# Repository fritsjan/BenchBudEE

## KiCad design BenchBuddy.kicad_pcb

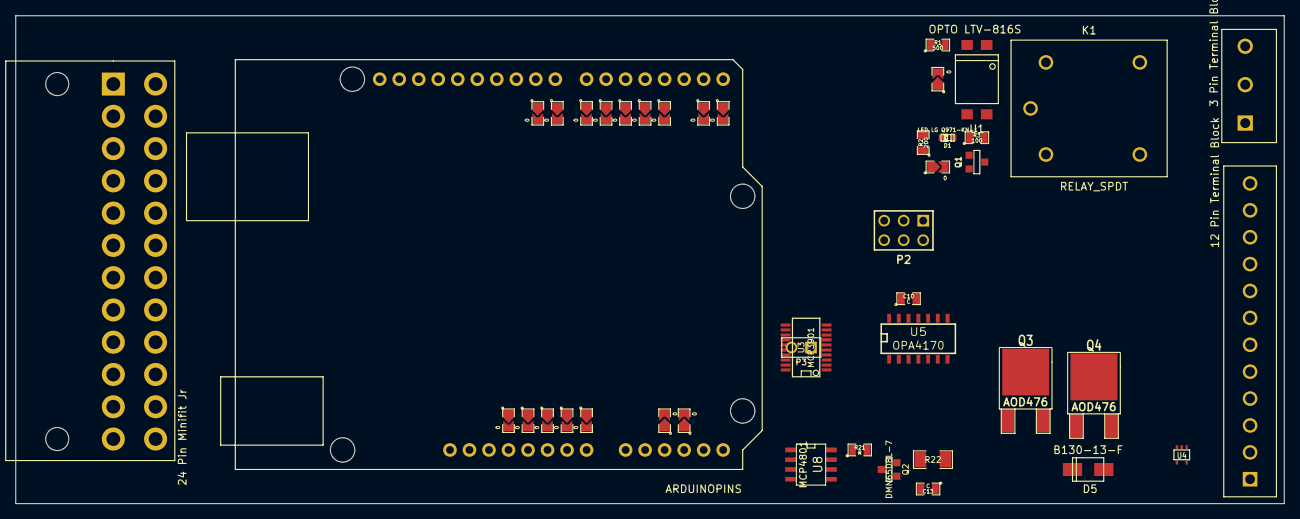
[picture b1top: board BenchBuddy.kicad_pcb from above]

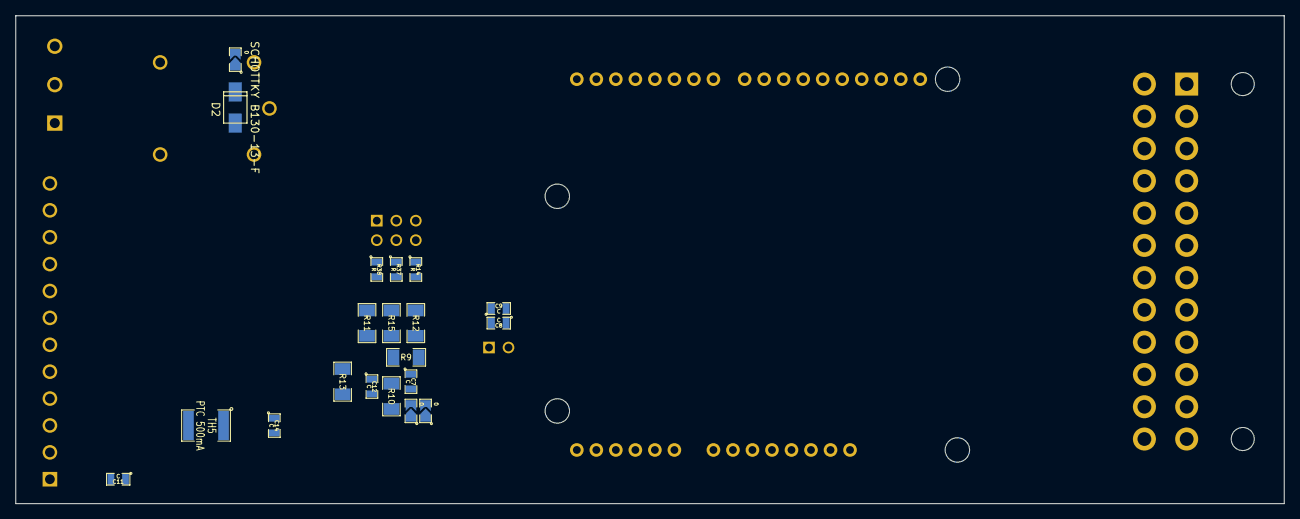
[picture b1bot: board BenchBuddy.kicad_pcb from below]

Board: 4 copper layers, 165.1 x 63.5 mm, 63 parts (20 on the bottom side), 66 nets, no tracks yet.

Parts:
C7, C8, C9, C10, C11, C12, C13, C14: C; SM0805
D1: LED LG Q971-KN-1; LED-0603
D2: SCHOTTKY B130-13-F; SMA
D5: B130-13-F; SMA
K1: RELAY_SPDT; TE-SPDT
K2: 3 Pin Terminal Block; 3pinTB
P1: 24 Pin Minifit Jr; 24pin-ATX
P2: CONN_3X2; pin_array_3x2
P3: CONN_2; PIN_ARRAY_2X1
P4: 12 Pin Terminal Block; 12pinTB
Q1: MMBT3904-7-F; SOT23EBC
Q2: DMN65D8L-7; SOT23GDS
Q3, Q4: AOD476; DPAK2
R1: 500; SM0805
R2: 200; SM0805
R3: 100; SM0805
R4, R5, R6, R23, R24, R25, R26, R27, R28, R29, R30, R31, R32, R33, R34, R35, R36, R39, R40, R41, R42: 0; S_Jumper_SM0805
R9, R10, R11, R12, R13, R15: R; SM1206
R14, R21, R37, R38: R; SM0805
R22: 1; SM1206
TH5: PTC 500mA; SM1812
U1: OPTO LTV-816S; 4-SMD
U3: MCP3901; SSOP20
U4: LMT84; SOT353
U5: OPA4170; SO14E
U8: MCP4801; SO8E
U10: ARDUINOPINS; ArduinoUnoR3

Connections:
+5V: C8.2, C9.1, C11.1, C13.2, P4.1, U3.2, U3.3, U4.4, U8.1
+12C: C14.2, P1.10, TH5.1
+12P: R4.2, R6.2, R23.1
+12V: C12.1, U5.4
-12V: C10.2, U5.11
/Arduino/CURR_MEAS: Q3.2, Q4.3, R22.1, R26.1
/Arduino/FAN_MODE: Q3.1, R36.2
/Arduino/FAN_PWM_N: Q2.G, R31.2
/Arduino/MISO: R30.2, U3.19
/Arduino/MOSI: R29.2, U3.20, U8.4
/Arduino/RELAY+: R35.2, U1.1
/Arduino/SCLK: R28.2, U3.18, U8.3
/Arduino/~ADC_CS: R33.2, U3.17
/Arduino/~DR: R40.2, U3.14
/Fan/CS_N: R34.2, U8.2
/Fan/FAN_OUT+: D5.2, TH5.2
/Fan/FAN_OUT-: D5.1, Q4.2
/Relay/RELAY_COM: K1.1, K2.1
/Relay/RELAY_NC: K1.4, K2.2
/TerminalBlock/RELAY_NC: K1.3, K2.3
/Thermalcouple/CH0+: C7.1, R9.1, U3.4, U5.1
/Thermalcouple/CH0-: C7.2, R42.2, U3.5
/Thermalcouple/CH1+: U3.6, U4.3
/Thermalcouple/CH1-: R41.2, U3.7
/Thermalcouple/TC IN +: P4.11, U5.10
AGND: C8.1, C9.2, C10.1, C11.2, C12.2, C13.1, C14.1, Q2.S, Q3.3, R10.1, R22.2, R41.1, R42.1, U3.8, U3.11, U4.1, U4.2, U4.5, U8.7
GND: P1.3, P1.5, P4.3, R1.1, R2.1, R5.1
unnamed: R35.1, U10.12
unnamed: R36.1, U10.11
unnamed: R31.1, U10.21
unnamed: R33.1, U10.19
unnamed: R27.2, U10.8
unnamed: R26.2, U10.7
unnamed: R39.1, U10.16
unnamed: R23.2, U10.4
unnamed: R40.1, U10.15
unnamed: R28.1, U10.24
unnamed: R25.2, U10.6
unnamed: R24.2, U10.5
unnamed: R30.1, U10.22
unnamed: R29.1, U10.23
unnamed: R34.1, U10.18
unnamed: R32.1, U10.20
unnamed: P2.1, P2.3, P2.5, R13.2, U5.9
unnamed: P2.4, R37.1
unnamed: R12.2, R15.2, U5.14
unnamed: R11.2, R13.1, U5.8
unnamed: R10.2, R12.1, U5.3
unnamed: R14.2, R15.1, R37.2, R38.2, U5.13
unnamed: P2.2, R38.1
unnamed: P2.6, R14.1
unnamed: P3.2, U3.12
unnamed: R9.2, R11.1, U5.2
unnamed: P3.1, U3.13
unnamed: R4.1, U1.4
unnamed: D2.1, K1.5, Q1.3
unnamed: R1.2, U1.2
unnamed: D1.1, R3.1, U1.3
unnamed: Q1.1, R5.2
unnamed: Q1.2, R3.2
unnamed: D1.2, R2.2
unnamed: D2.2, K1.2, R6.1
unnamed: P1.4, P1.6
unnamed: P1.1, P1.2
unnamed: R21.1, U8.8
unnamed: Q2.D, R21.2

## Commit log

2014-02-02 Creation of initial blank files
2014-02-02 creating schematic skeleton
2014-02-03 Definging inputs and outputs
2014-02-04 Thermal Couple placeholder
2014-02-04 Tried my own Current Driver Diagram
2014-02-06 fan/currentdriver after chris video
2014-02-06 Try on relay circuit
2014-02-06 Relay circuit
2014-02-06 Power circuit
2014-02-07 try out power control
2014-02-07 after power adjustment video
2014-02-07 After led drier module
2014-02-07 arduino module / hooking things up
2014-02-10 currentfan revisited
2014-02-22 associating and placing relay module
2014-02-23 associating-and-placing-the-thermocouple-module
2014-02-23 associating-and-placing-the-terminal-atx-blocks
2014-02-23 associating-and-placing-the-terminalatx-blocks
2014-02-24 associating-and-placing-arduino-module
2014-02-25 fan module
